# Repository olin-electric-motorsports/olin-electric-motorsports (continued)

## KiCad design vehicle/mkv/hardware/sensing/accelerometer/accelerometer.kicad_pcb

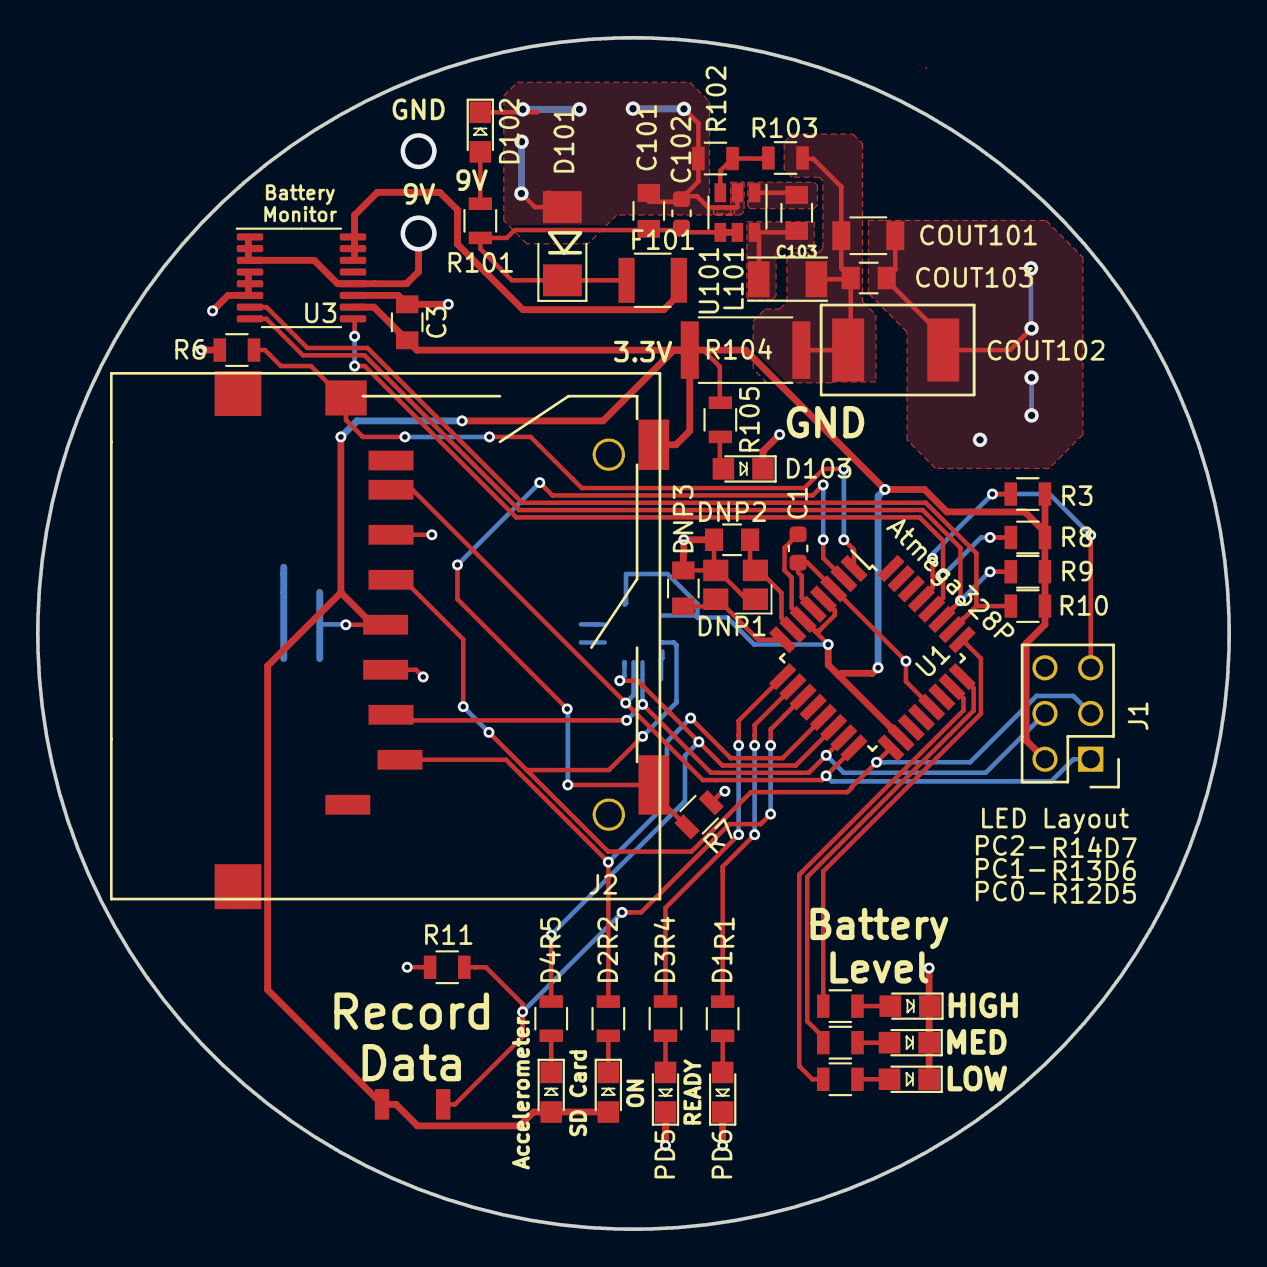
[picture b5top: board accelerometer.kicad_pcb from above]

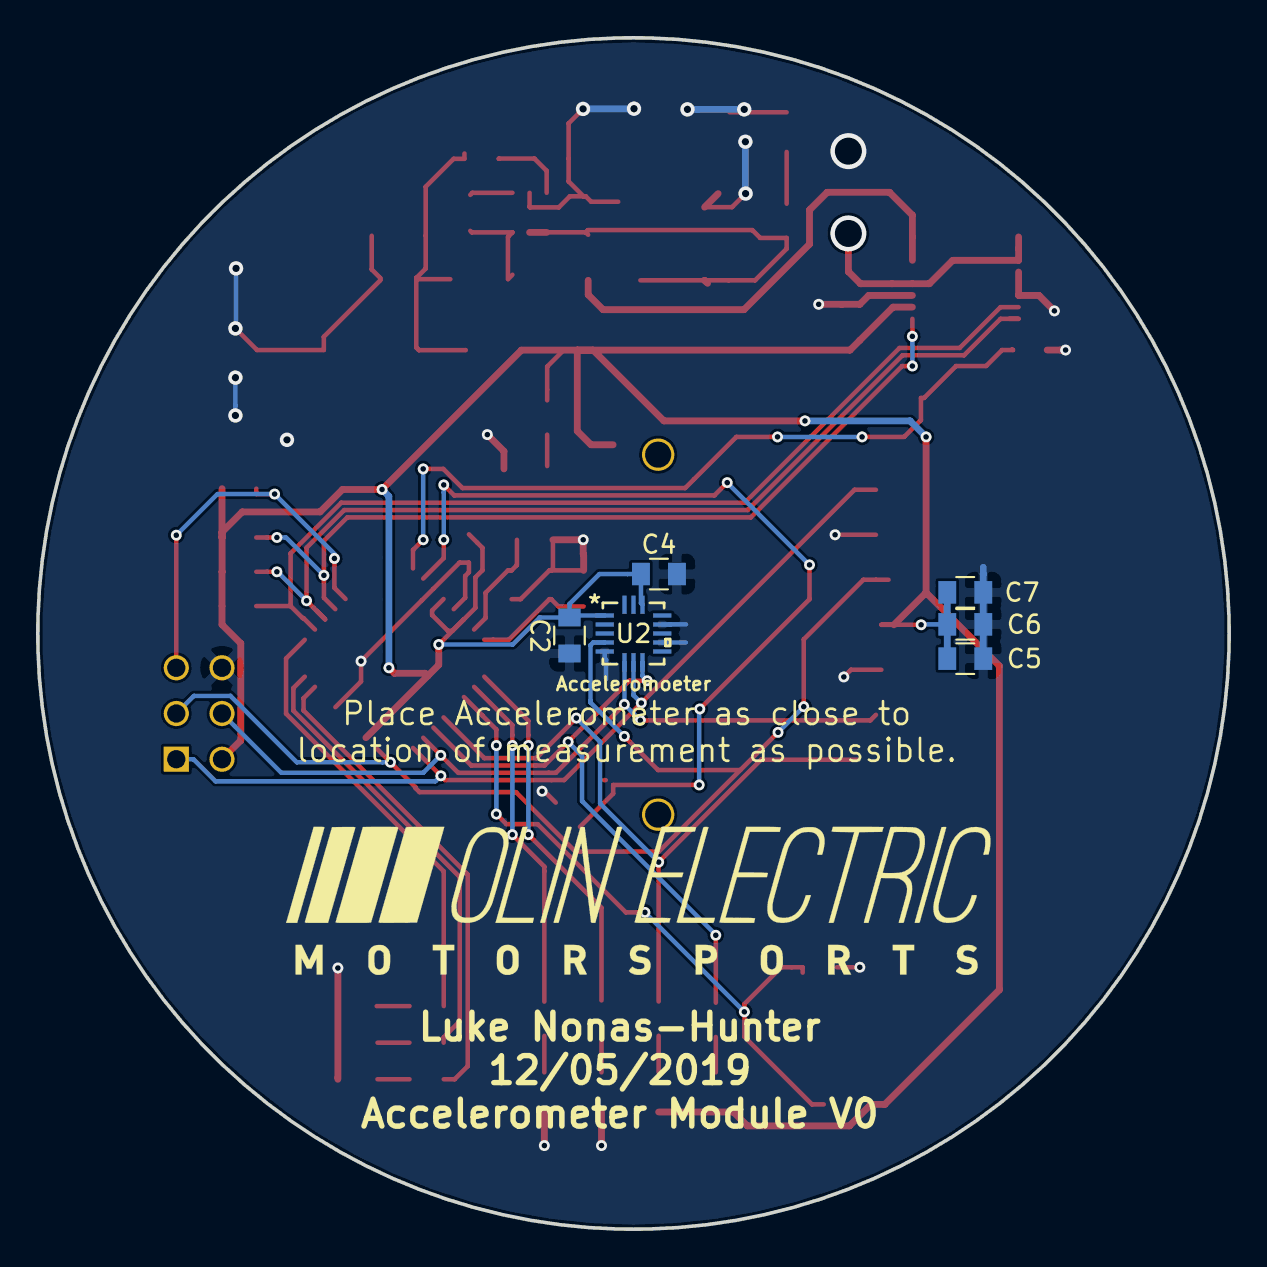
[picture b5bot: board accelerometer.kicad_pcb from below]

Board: 2 copper layers, 66.2 x 66.2 mm, 54 parts (6 on the bottom side), 37 nets.

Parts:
C1: C_100nF; C_0603_1608Metric
C2, C5: C_10uF; C_0805_OEM
C3, C4, C7, C101, C103: C_0.1uF; C_0805_OEM
C6: C_1uF; C_0805_OEM
C102: C_4.7uF; C_0603_1608Metric
COUT101: C_22uF; C_1206_OEM
COUT102: C_33uF; Fuse_1812
COUT103: C_47uF; C_0805_OEM
D1, D2, D4: LED_0805_Red; LED_0805_OEM
D3, D5, D6, D7, D102, D103: LED_0805; LED_0805_OEM
D101: D_Zener_18V; DO-214AA
DNP1: Crystal_SMD; Crystal_SMD_FA238
DNP2, DNP3: C_30pF; C_0805_OEM
F101: F_500mA_16V; Fuse_1210
J1: CONN_02X03; Pin_Header_Straight_2x03
J2: SD_socket; sd_socket_molex_5009980900
L101: L_15uH; L_100uH_OEM
R1, R2, R4, R5, R12, R13, R14, R105: R_100; R_0805_OEM
R3, R6, R7, R8, R9, R10, R11: R_10K; R_0805_OEM
R101: R_499; R_0805_OEM
R102: R_25K; R_0805_OEM
R103: R_54.9K; R_0805_OEM
R104: R_0_2512; R_2512_OEM
SW1: SW_Push_SPST_NO; SW_B3U-1000P_4.2x1.7mm
U1: ATmega328P-AU; TQFP-32_7x7mm_P0.8mm
U2: LGA-16_3x3x1mm; LIS3DHTR
U3: INA260; TSSOP-16_4.4x5mm_P0.65mm
U101: TPS560430YF; SOT-23-6_OEM

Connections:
/9V_in: U3.1, U3.2, U3.3, U3.12
/9V_out: F101.2, U3.14, U3.15, U3.16
/ALERT: R10.2, U1.26, U3.7
/CS: R5.1, U1.14, U2.8
/CS_SD: J2.1, R2.2, U1.13
/Detect: J2.12, R7.1, U1.2
/MISO: J1.1, J2.7, U1.16, U2.7
/MOSI: J1.4, J2.2, U1.15, U2.6
/PC0: R12.1, U1.23
/PC1: R13.1, U1.24
/PC2: R14.1, U1.25
/Protect: J2.11, R6.1, U1.1
/RESET: J1.5, R3.2, U1.29
/SCK: J1.3, J2.5, U1.17, U2.4
/SCL: R8.2, U1.28, U3.9
/SDA: R9.2, U1.27, U3.8
GND: C1.1, C2.1, C3.1, C4.2, C5.2, C6.2, C7.2, C101.2, C102.2, COUT101.2, COUT102.2, COUT103.2, D1.1, D3.1, D5.1, D6.1, D7.1, D101.2, D102.1, D103.1, DNP1.2, DNP1.4, DNP2.2, DNP3.2, J1.6, J2.3, J2.6, R6.2, R7.2, R11.2, R102.2, U1.3, U1.5, U1.21, U2.5, U2.10, U2.12, U3.4, U3.5, U3.6, U3.11, U101.2
unnamed: C101.1, C102.1, D101.1, F101.1, R101.1, U101.4, U101.5
unnamed: C103.1, U101.1
unnamed: C103.2, L101.1, U101.6
unnamed: COUT101.1, COUT102.1, COUT103.1, L101.2, R103.1, R104.1
unnamed: D1.2, R1.2
unnamed: D2.1, R2.1
unnamed: D3.2, R4.1
unnamed: D4.1, R5.2
unnamed: D5.2, R12.2
unnamed: D6.2, R13.2
unnamed: D7.2, R14.2
unnamed: D102.2, R101.2
unnamed: D103.2, R105.2
unnamed: DNP1.1, DNP2.1, U1.7
unnamed: DNP1.3, DNP3.1, U1.8
unnamed: R1.1, U1.10
unnamed: R4.2, U1.9
unnamed: R11.1, SW1.1, U1.11
unnamed: R102.1, R103.2, U101.3
VCC: C1.2, C2.2, C3.2, C4.1, C5.1, C6.1, C7.1, D2.2, D4.2, J1.2, J2.4, J2.10, R3.1, R8.1, R9.1, R10.1, R104.2, R105.1, SW1.2, U1.4, U1.6, U1.18, U2.1, U2.14, U3.10

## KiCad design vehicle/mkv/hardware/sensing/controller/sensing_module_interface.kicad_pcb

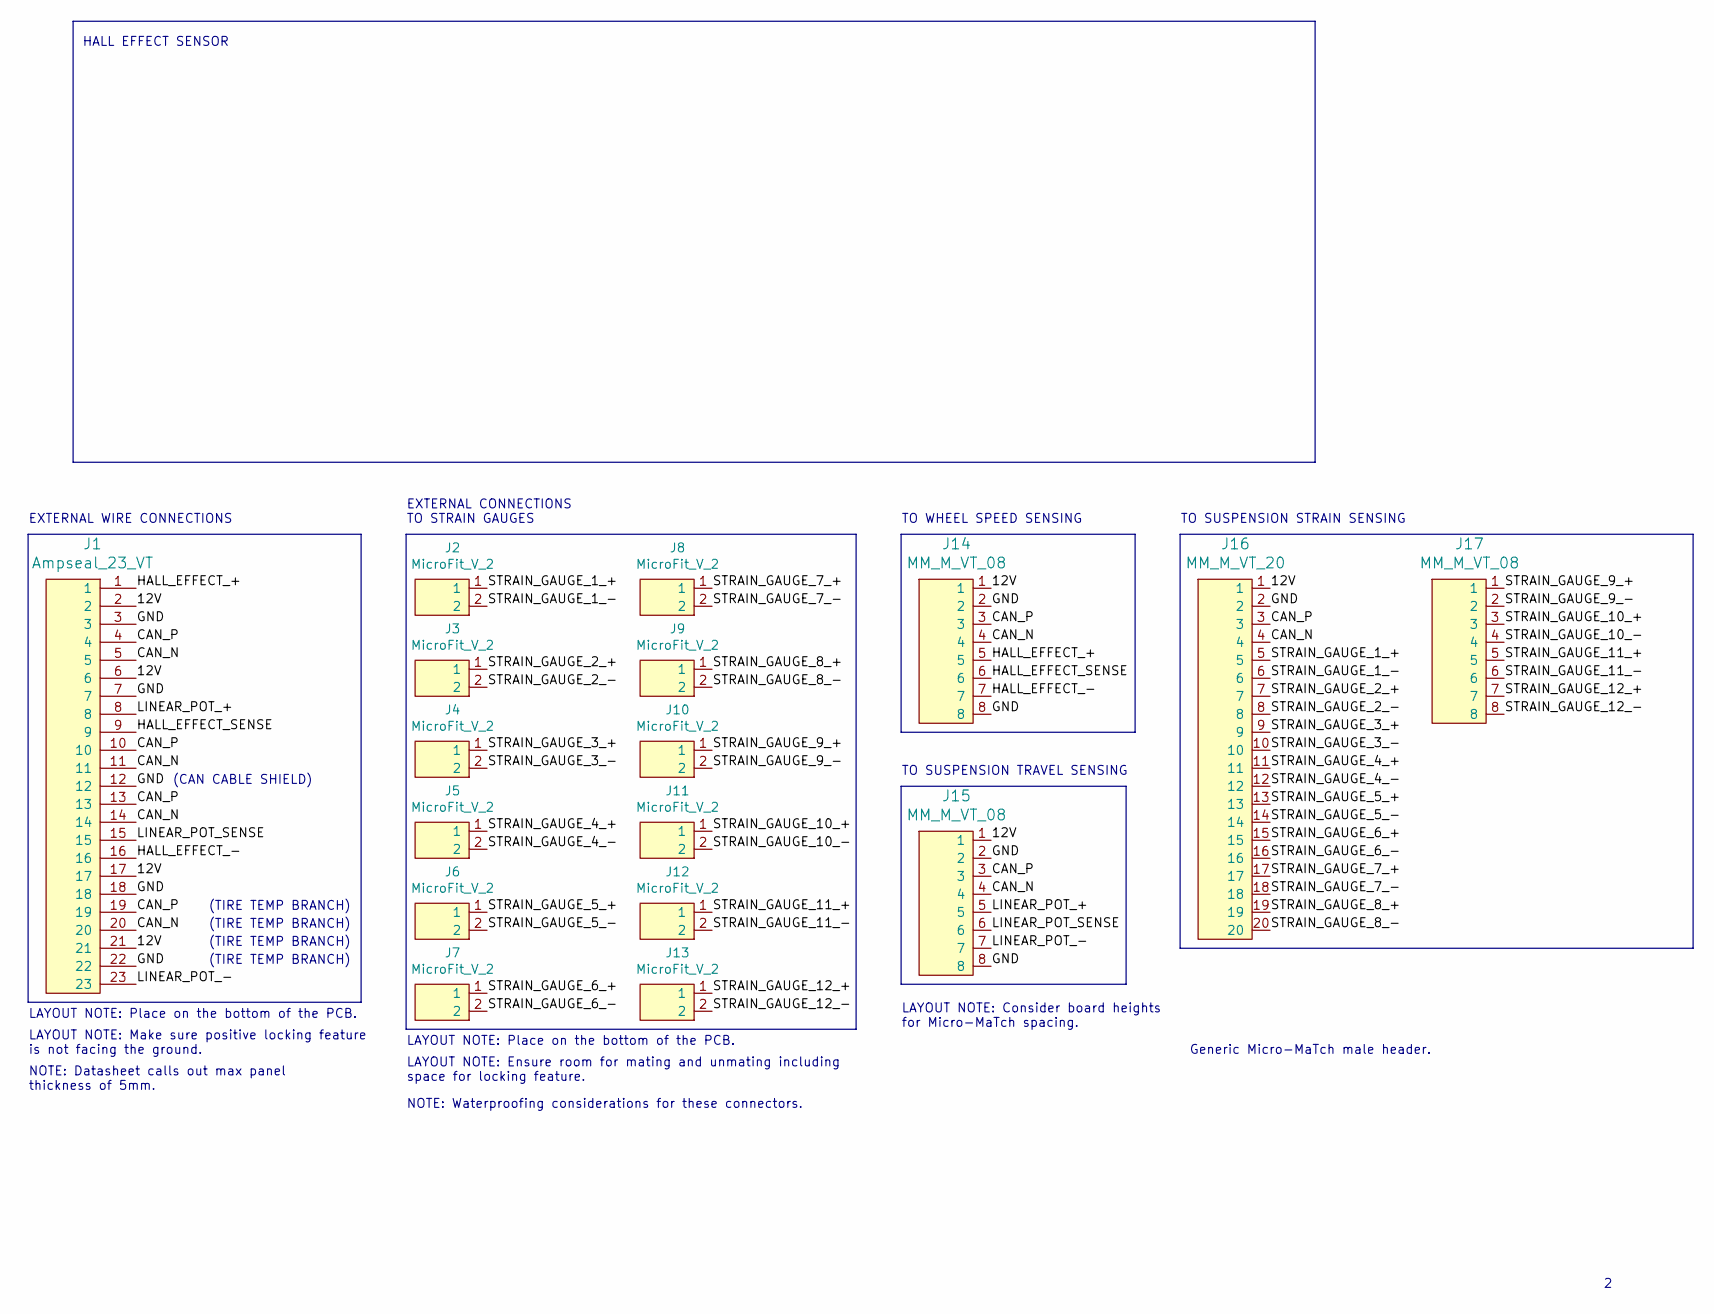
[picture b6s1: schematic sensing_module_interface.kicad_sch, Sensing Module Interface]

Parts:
J1: Ampseal_23_VT; Ampseal_23; MPN 776228-1
J2, J3, J4, J5, J6, J7, J8, J9, J10, J11, J12, J13: MicroFit_V_2; MPN WM10660-ND
J14, J15, J17: MM_M_VT_08; micromatch_female_ra_8; MPN 215464-8
J16: MM_M_VT_20; micromatch_female_ra_20; MPN 2-215464-0

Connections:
/12V: J1.2, J1.6, J1.17, J1.21, J14.1, J15.1, J16.1
/CAN_N: J1.5, J1.11, J1.14, J1.20, J14.4, J15.4, J16.4
/CAN_P: J1.4, J1.10, J1.13, J1.19, J14.3, J15.3, J16.3
/GND: J1.3, J1.7, J1.12, J1.18, J1.22, J14.2, J14.8, J15.2, J15.8, J16.2
/HALL_EFFECT_+: J1.1, J14.5
/HALL_EFFECT_-: J1.16, J14.7
/HALL_EFFECT_SENSE: J1.9, J14.6
/LINEAR_POT_+: J1.8, J15.5
/LINEAR_POT_-: J1.23, J15.7
/LINEAR_POT_SENSE: J1.15, J15.6
/STRAIN_GAUGE_1_+: J2.1, J16.5
/STRAIN_GAUGE_1_-: J2.2, J16.6
/STRAIN_GAUGE_2_+: J3.1, J16.7
/STRAIN_GAUGE_2_-: J3.2, J16.8
/STRAIN_GAUGE_3_+: J4.1, J16.9
/STRAIN_GAUGE_3_-: J4.2, J16.10
/STRAIN_GAUGE_4_+: J5.1, J16.11
/STRAIN_GAUGE_4_-: J5.2, J16.12
/STRAIN_GAUGE_5_+: J6.1, J16.13
/STRAIN_GAUGE_5_-: J6.2, J16.14
/STRAIN_GAUGE_6_+: J7.1, J16.15
/STRAIN_GAUGE_6_-: J7.2, J16.16
/STRAIN_GAUGE_7_+: J8.1, J16.17
/STRAIN_GAUGE_7_-: J8.2, J16.18
/STRAIN_GAUGE_8_+: J9.1, J16.19
/STRAIN_GAUGE_8_-: J9.2, J16.20
/STRAIN_GAUGE_9_+: J10.1, J17.1
/STRAIN_GAUGE_9_-: J10.2, J17.2
/STRAIN_GAUGE_10_+: J11.1, J17.3
/STRAIN_GAUGE_10_-: J11.2, J17.4
/STRAIN_GAUGE_11_+: J12.1, J17.5
/STRAIN_GAUGE_11_-: J12.2, J17.6
/STRAIN_GAUGE_12_+: J13.1, J17.7
/STRAIN_GAUGE_12_-: J13.2, J17.8

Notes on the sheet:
Generic Micro-MaTch male header.
(TIRE TEMP BRANCH)
NOTE: Waterproofing considerations for these connectors.
LAYOUT NOTE: Make sure positive locking feature is not facing the ground.
TO SUSPENSION STRAIN SENSING
EXTERNAL CONNECTIONS TO STRAIN GAUGES
LAYOUT NOTE: Place on the bottom of the PCB.
(CAN CABLE SHIELD)
LAYOUT NOTE: Consider board heights for Micro-MaTch spacing.
HALL EFFECT SENSOR
LAYOUT NOTE: Ensure room for mating and unmating including space for locking feature.
EXTERNAL WIRE CONNECTIONS
TO WHEEL SPEED SENSING
TO SUSPENSION TRAVEL SENSING
NOTE: Datasheet calls out max panel thickness of 5mm.

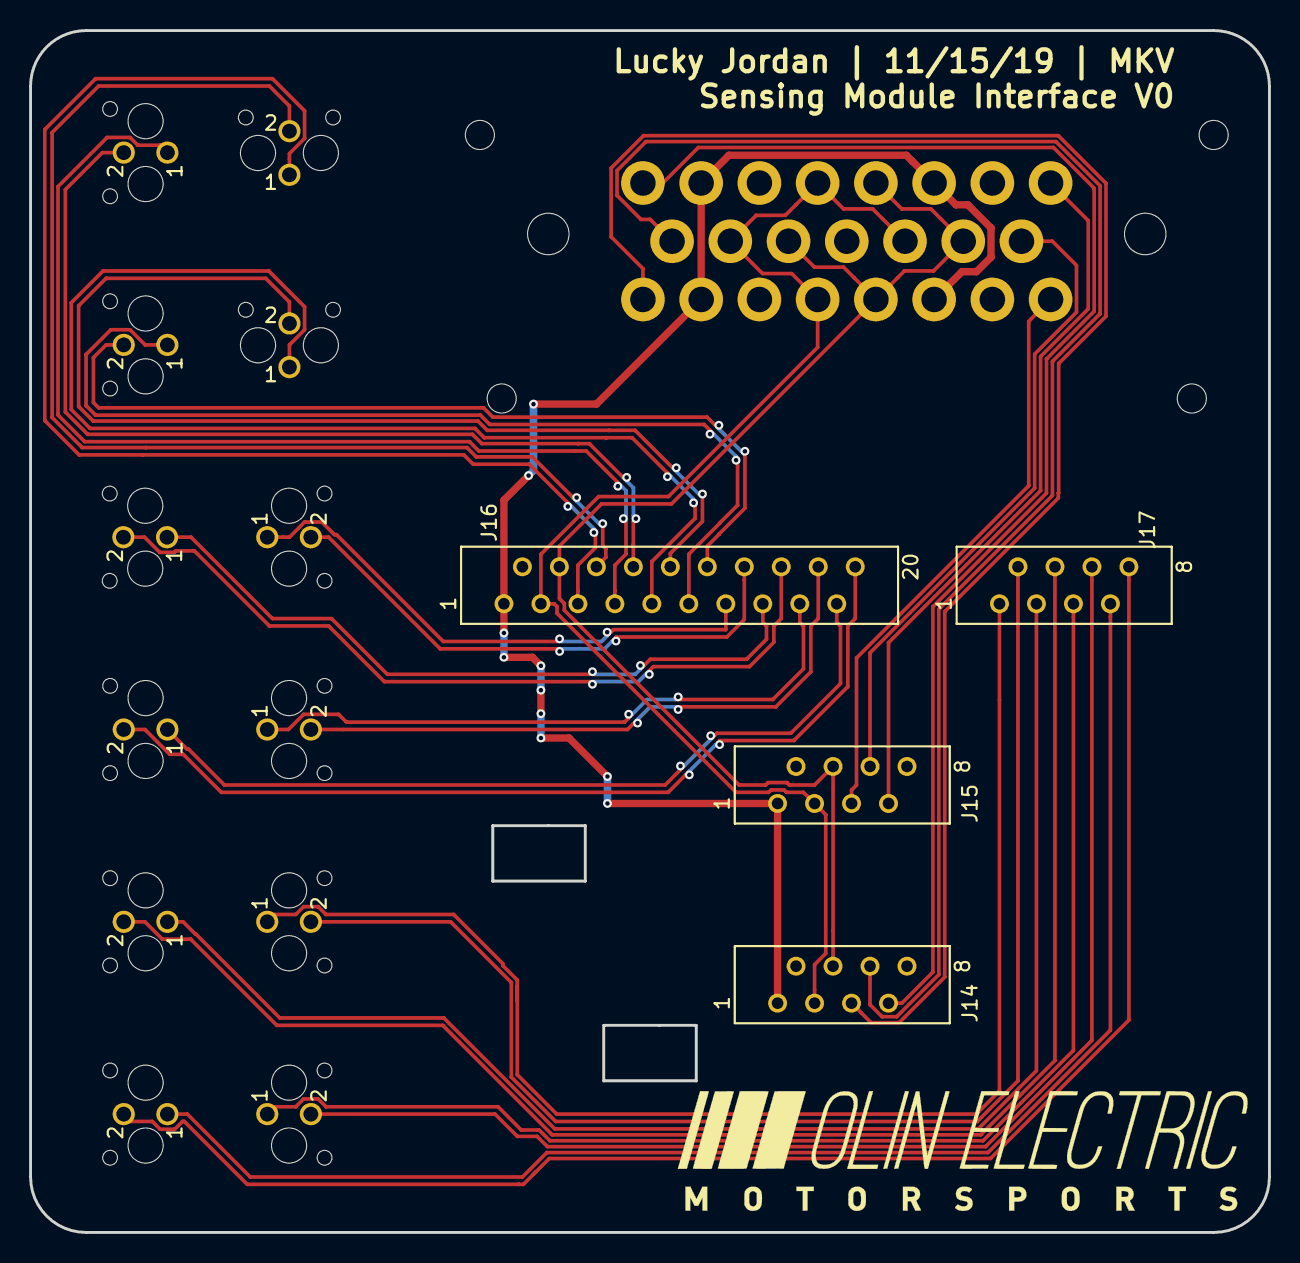
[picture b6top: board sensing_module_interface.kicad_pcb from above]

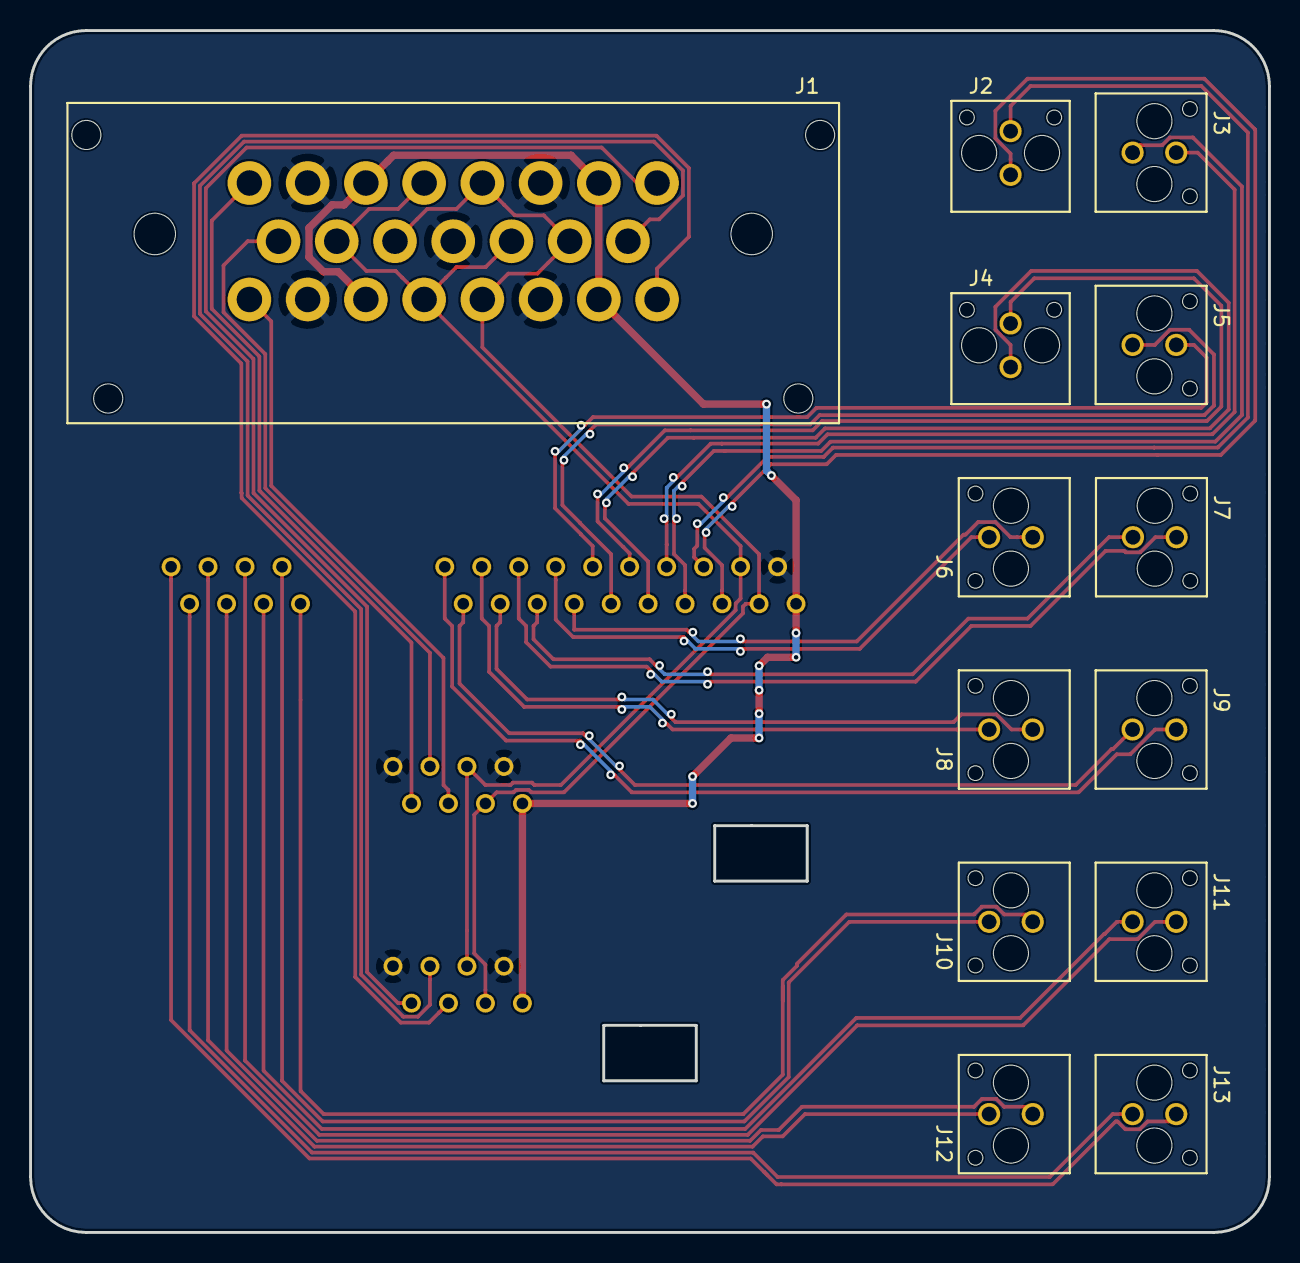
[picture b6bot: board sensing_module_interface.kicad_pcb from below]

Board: 2 copper layers, 85.1 x 82.5 mm, 17 parts (13 on the bottom side), 34 nets.

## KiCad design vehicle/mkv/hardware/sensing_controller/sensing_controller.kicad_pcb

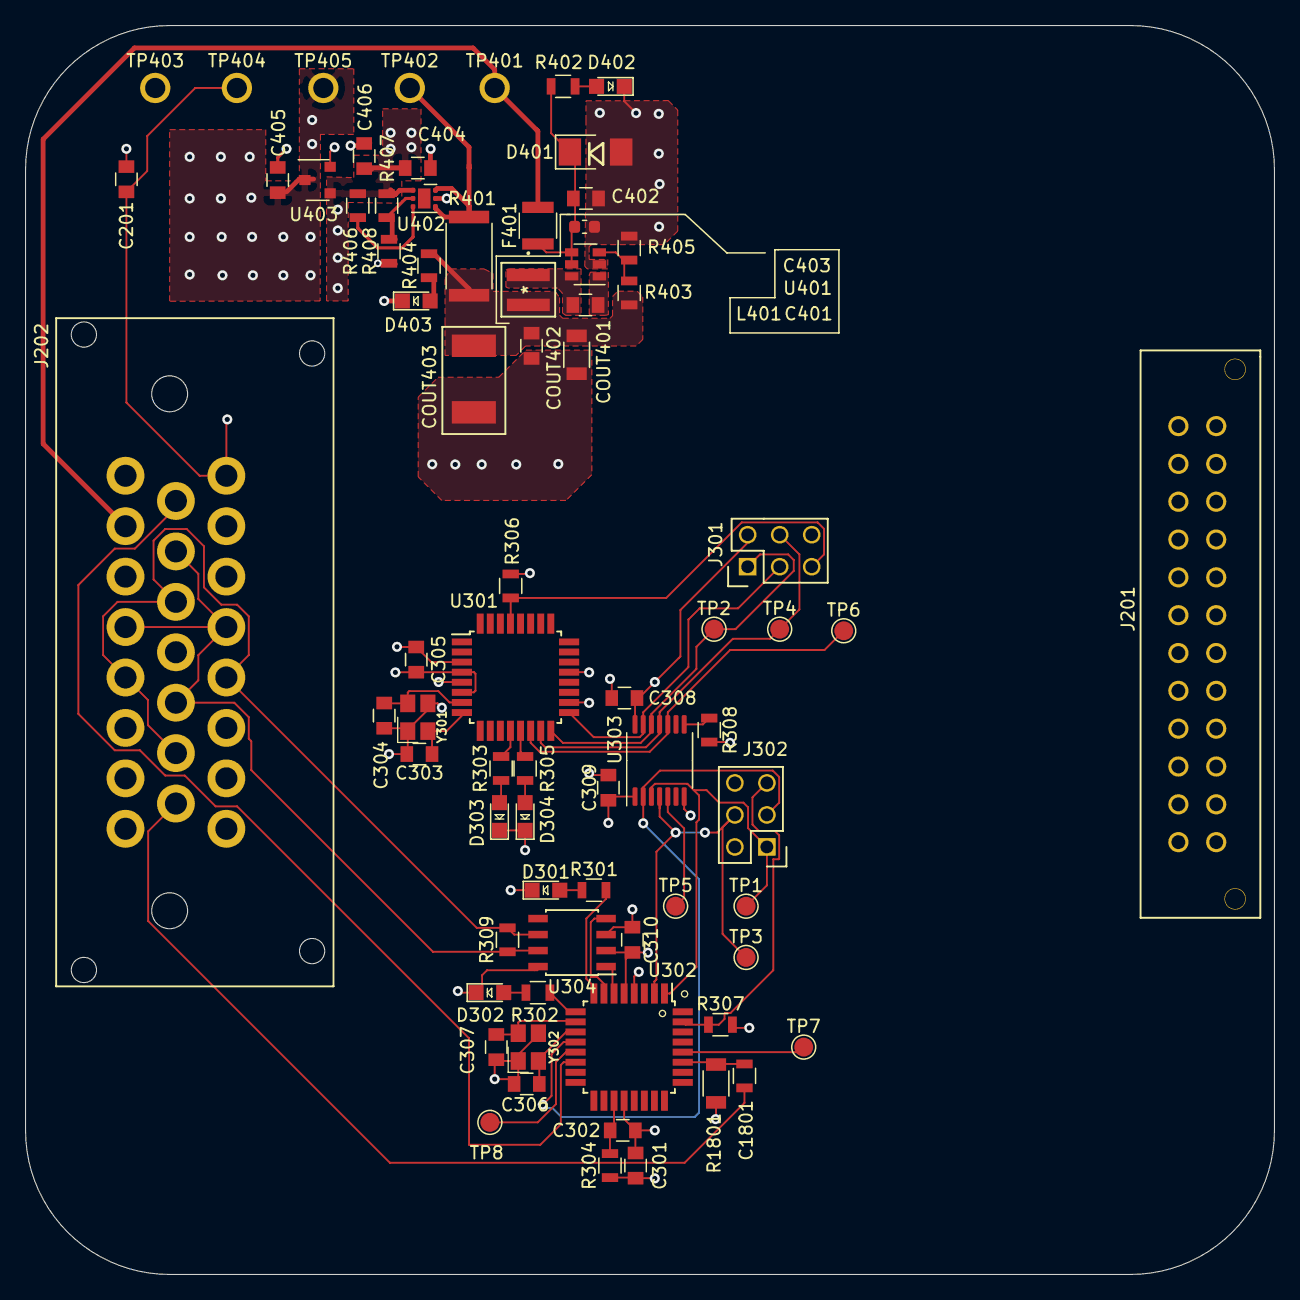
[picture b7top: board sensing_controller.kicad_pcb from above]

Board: 4 copper layers, 99.1 x 99.1 mm, 74 parts (0 on the bottom side), 47 nets.

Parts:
C201, C301, C305, C308, C309, C310, C401, C402, C405, C406: C_0.1uF; C_0805_OEM
C302: C_100pF; C_0805_OEM
C303, C304, C306, C307: C_30pF; C_0805_OEM
C403: C_2.2uF; C_0603_1608Metric
C404: C_47uF; C_0805_OEM
C1801: C_22uF; C_1206_OEM
COUT401: C_22uF; C_1206_OEM
COUT402: C_47uF; C_0805_OEM
COUT403: C_33uF; Fuse_1812
D301, D302, D303, D304, D402, D403: LED_0805; LED_0805_OEM
D401: D_Zener_18V; DO-214AA
F401: F_500mA_16V; Fuse_1210
J201: MicroFit_24; Molex_Microfit3_Header_02x12_Straight_0444322401_OEM
J202: Ampseal_23_RA; Ampseal_23
J301, J302: CONN_02X03; Pin_Header_Straight_2x03
L401: L_8.1uH
R301, R302, R303, R305, R404: R_200; R_0805_OEM
R304: R_100; R_0805_OEM
R306, R307, R308, R406: R_10K; R_0805_OEM
R309: R_120_DNP; R_0805_OEM
R401: R_0_2512; R_2512_OEM
R402: R_1K; R_0805_OEM
R403: R_90k; R_0805_OEM
R405: R_15k; R_0805_OEM
R407: R_300K; R_0805_OEM
R408: R_100K; R_0805_OEM
R1801: R_1K_0.1; R_0805_OEM
TP1, TP2, TP3, TP4, TP5, TP6, TP7, TP8: Test_Point_SMD; TestPoint_Pad_D1.5mm
TP401, TP402, TP403, TP404, TP405: TP; tp_1.6mm
U301: ATmega328P-AU; TQFP-32_7x7mm_P0.8mm
U302: ATMEGA16M1; TQFP-32_7x7mm_Pitch0.8mm
U303: TXB0104; TSSOP-14_4.4x5mm_P0.65mm
U304: MCP2561-E_SN; SOIC-8_3.9x4.9mm_Pitch1.27mm_OEM
U401: TPS560430YF; SOT-23-6_OEM
U402: TPS7A26
U403: LM3480; SOT-23-3_OEM
Y301, Y302: Crystal_SMD; Crystal_SMD_FA238

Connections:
3.3V: C305.1, C308.2, C405.1, J301.2, R306.1, TP405.1, U301.4, U301.6, U301.18, U303.14, U403.1
5V: C201.2, C301.1, C309.1, C310.1, C404.1, C406.1, J202.1, J202.8, J302.2, R304.1, R307.2, R308.2, R406.2, R407.1, TP404.1, U302.4, U303.1, U304.3, U402.1, U403.2
7V: R401.1, TP402.1, U402.4, U402.6
12V: F401.2, J202.2, J202.6, J202.17, J202.21, TP401.1
/micros/CAN_RX: U302.7, U304.4
/micros/CAN_TX: U302.6, U304.1
/micros/PM_CS: TP5.1, U303.5
/micros/PM_MISO: J302.1, TP1.1, U302.1, U303.3
/micros/PM_MOSI: J302.4, TP3.1, U302.2, U303.4
/micros/PM_RESET: J302.5, R307.1, U302.31
/micros/PM_SCK: J302.3, U302.12, U303.2
/micros/SM_CS: TP6.1, U301.14, U303.10
/micros/SM_MISO: J301.1, TP2.1, U301.16, U303.12
/micros/SM_MOSI: J301.4, TP4.1, U301.15, U303.11
/micros/SM_RESET: J301.5, R306.2, U301.29
/micros/SM_SCK: J301.3, U301.17, U303.13
CAN+: J202.4, J202.10, J202.13, J202.19, R309.1, U304.7
CAN-: J202.5, J202.11, J202.14, J202.20, R309.2, U304.6
FRONT_SENSE: TP7.1, U302.28
GND: C201.1, C301.2, C302.2, C303.2, C304.2, C305.2, C306.2, C307.2, C308.1, C309.2, C310.2, C402.1, C403.2, C404.2, C405.2, C406.2, C1801.2, COUT401.1, COUT402.2, COUT403.2, D301.1, D302.1, D303.1, D304.1, D401.2, D402.1, D403.1, J201.13, J201.14, J201.15, J201.16, J201.17, J201.18, J201.19, J201.20, J201.21, J201.22, J201.23, J201.24, J202.3, J202.7, J202.12, J202.16, J202.18, J202.22, J202.23, J301.6, J302.6, R405.2, R408.2, TP403.1, U301.3, U301.5, U301.21, U302.5, U302.20, U303.7, U304.2, U304.8, U401.2, U402.5, U403.3, Y301.2, Y301.4, Y302.2, Y302.4
HALL_EFFECT_SENSE: J202.9, U302.14
LEFT_SENSE: TP8.1, U302.13
LIN_POT_SENSE: J202.15, R1801.1
LIN_POT_SENSE_FILTERED: C1801.1, R1801.2, U302.27
unnamed: C302.1, R304.2, U302.19
unnamed: C303.1, U301.8, Y301.1
unnamed: C304.1, U301.7, Y301.3
unnamed: C306.1, U302.11, Y302.1
unnamed: C307.1, U302.10, Y302.3
unnamed: C401.1, L401.1, U401.6
unnamed: C401.2, U401.1
unnamed: C402.2, C403.1, D401.1, F401.1, R402.1, U401.4, U401.5
unnamed: COUT401.2, COUT402.1, COUT403.1, L401.2, R401.2, R403.1, R404.1
unnamed: D301.2, R301.1
unnamed: D302.2, R302.1
unnamed: D303.2, R303.1
unnamed: D304.2, R305.1
unnamed: D402.2, R402.2
unnamed: D403.2, R404.2
unnamed: R301.2, U302.8
unnamed: R302.2, U302.9
unnamed: R303.2, U301.12
unnamed: R305.2, U301.13
unnamed: R308.1, U303.8
unnamed: R403.2, R405.1, U401.3
unnamed: R407.2, R408.1, U402.2
Vpg: R406.1, U402.3
